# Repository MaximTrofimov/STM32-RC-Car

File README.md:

# STM32-RC-Car
RC car with manual and autonomous modes, dual STM32 wireless communication (remote and car PCBs).

## Demo Videos

**Manual Mode**

**Autonomous Mode**

## Photos

**RC Car and Remote**

**Remote and Car PCBs**

## Overview
- Designed two custom PCBs (remote and car) for a wirelessly-controlled RC car
- Implemented wireless communication between two STM32 microcontrollers using embedded firmware (HAL library)
- Developed manual and autonomous modes

## Hardware
- STM32F446RE (x2 - one in car, one in remote)
- NucleoF446RE (x2 - prototyping)
- NRF24L01+PA+LNA wireless transceiver modules (x2 - one for car, one for remote)
- HC-SR04 ultrasonic sensor (x3 - front, left, right)
- SG90 servo motor (steering)
- TB6612FNG dual H-bridge motor driver (RWD)
- TT dual DC motor 3-6V (x2)
- KY-023 dual-axis analog joystick (remote)
- Custom PCBs (x2 - one for car, one for remote)
- 2S Lipo battery (car)
- 1s Li Ion battery (remote)

## Repo Structure
```
Firmware/
  car_mcu/       - STM32 embedded firmware for the car MCU
  remote_mcu/    - STM32 embedded firmware for the remote MCU
Hardware/
  car_pcb/       - Car PCB, schematic, BOM
  remote_pcb/    - Remote PCB, schematic, BOM
Mechanical/       - Wheels and steering servo enclosure CAD files (STEP)
```

## How It Works

**Manual Mode:**
The X and Y coordinates of the joystick position are read into a two variable array, VR. The array is then transmitted alongside each packet using the remote PCB's NRF24L01 module, and received at the car PCB's NRF24L01 module. The DC Motors are controlled using the TB6612FNG where a maximum joystick value results in fully duty cycle, a neutral results in zero duty cycle, and a minimum results in maximum duty cycle spinning the motors the other way. The SG90 steering is controlled via a timer for PWM. If the joystick is extended to the far right or far left, the NRF24L01 sends a larger joystick value and therefore the pulse is set to high for longer. Both throttle and steering respond to the specific displacement of the joystick from its absolute center, giving it the ability to control speed, and steering degree. The firmware dictates what part of the packet is responsible for motors, what part for the steering angle, and what part for the mode, which is triggered via an interrupt. 

**Autonomous Mode:**
If the joystick button is pressed, the mode is toggled to autonomous. Motors begin by running on half duty cycle and steering is set to a constant of about 20 degrees. The front, left, and right ultrasonic sensors notify the microcontroller when an obstacle is a certain distance away. Once this happens the car stops, checks its sides, goes back, and turns to the side where there is more free space. 

## Firmware Configuration

**Car MCU**

**Remote MCU**

## PCB Design

**Car PCB**

**Remote PCB**

## Breadboard Prototyping

## Power

**Car PCB**
- 2S Lipo -> 3.3V (500 mA rating, STM32, NRF24L01, TB6612FNG logic): TPS62152RGTR, reference schematic on Texas Instruments Power Designer.
- 2S Lipo -> 5V (2A rating, TB6612FNG motor power, SG90, HCSR04): TPS82130SILR, reference schematic on Texas Instruments Power Designer.

**Remote PCB**
- 1S Li-Ion -> 3.3V (600 mA rating, STM32, KY-023, NRF24L01): AP2112K-3.3TRG1, reference schematic on datasheet. Used LDO due to lower voltage difference. 

## Credits
- Shawn Hymel STM32 Tutorial Series [https://www.youtube.com/watch?v=hyZS2p1tW-g&list=PLEBQazB0HUyRYuzfi4clXsKUSgorErmBv]
- Phil's Lab KiCad Tutorial [https://www.youtube.com/watch?v=aVUqaB0IMh4]
- NRF24L01 Tutorial Series [https://www.youtube.com/watch?v=mB7LsiscM78&t=996s]
- HCSR04 Tutorial Article [https://controllerstech.com/hcsr04-ultrasonic-sensor-and-stm32/]
- SG90 Tutorial Article [https://controllerstech.com/servo-motor-with-stm32/]
- TB6612FNG Tutorial Video [https://www.youtube.com/watch?v=zWYYvtU8Wt4]
- Joystick Module Tutorial Article [https://controllerstech.com/joystick-and-stm32/]
- Texas Instruments 2S Lipo -> 3.3V Buck Converter Circuit [https://webench.ti.com/power-designer/switching-regulator/customize/5?noparams=0]
- Texas Instruments 2S Lipo -> 5V Buck Converter Circuit [https://webench.ti.com/power-designer/switching-regulator/customize/6?noparams=0]

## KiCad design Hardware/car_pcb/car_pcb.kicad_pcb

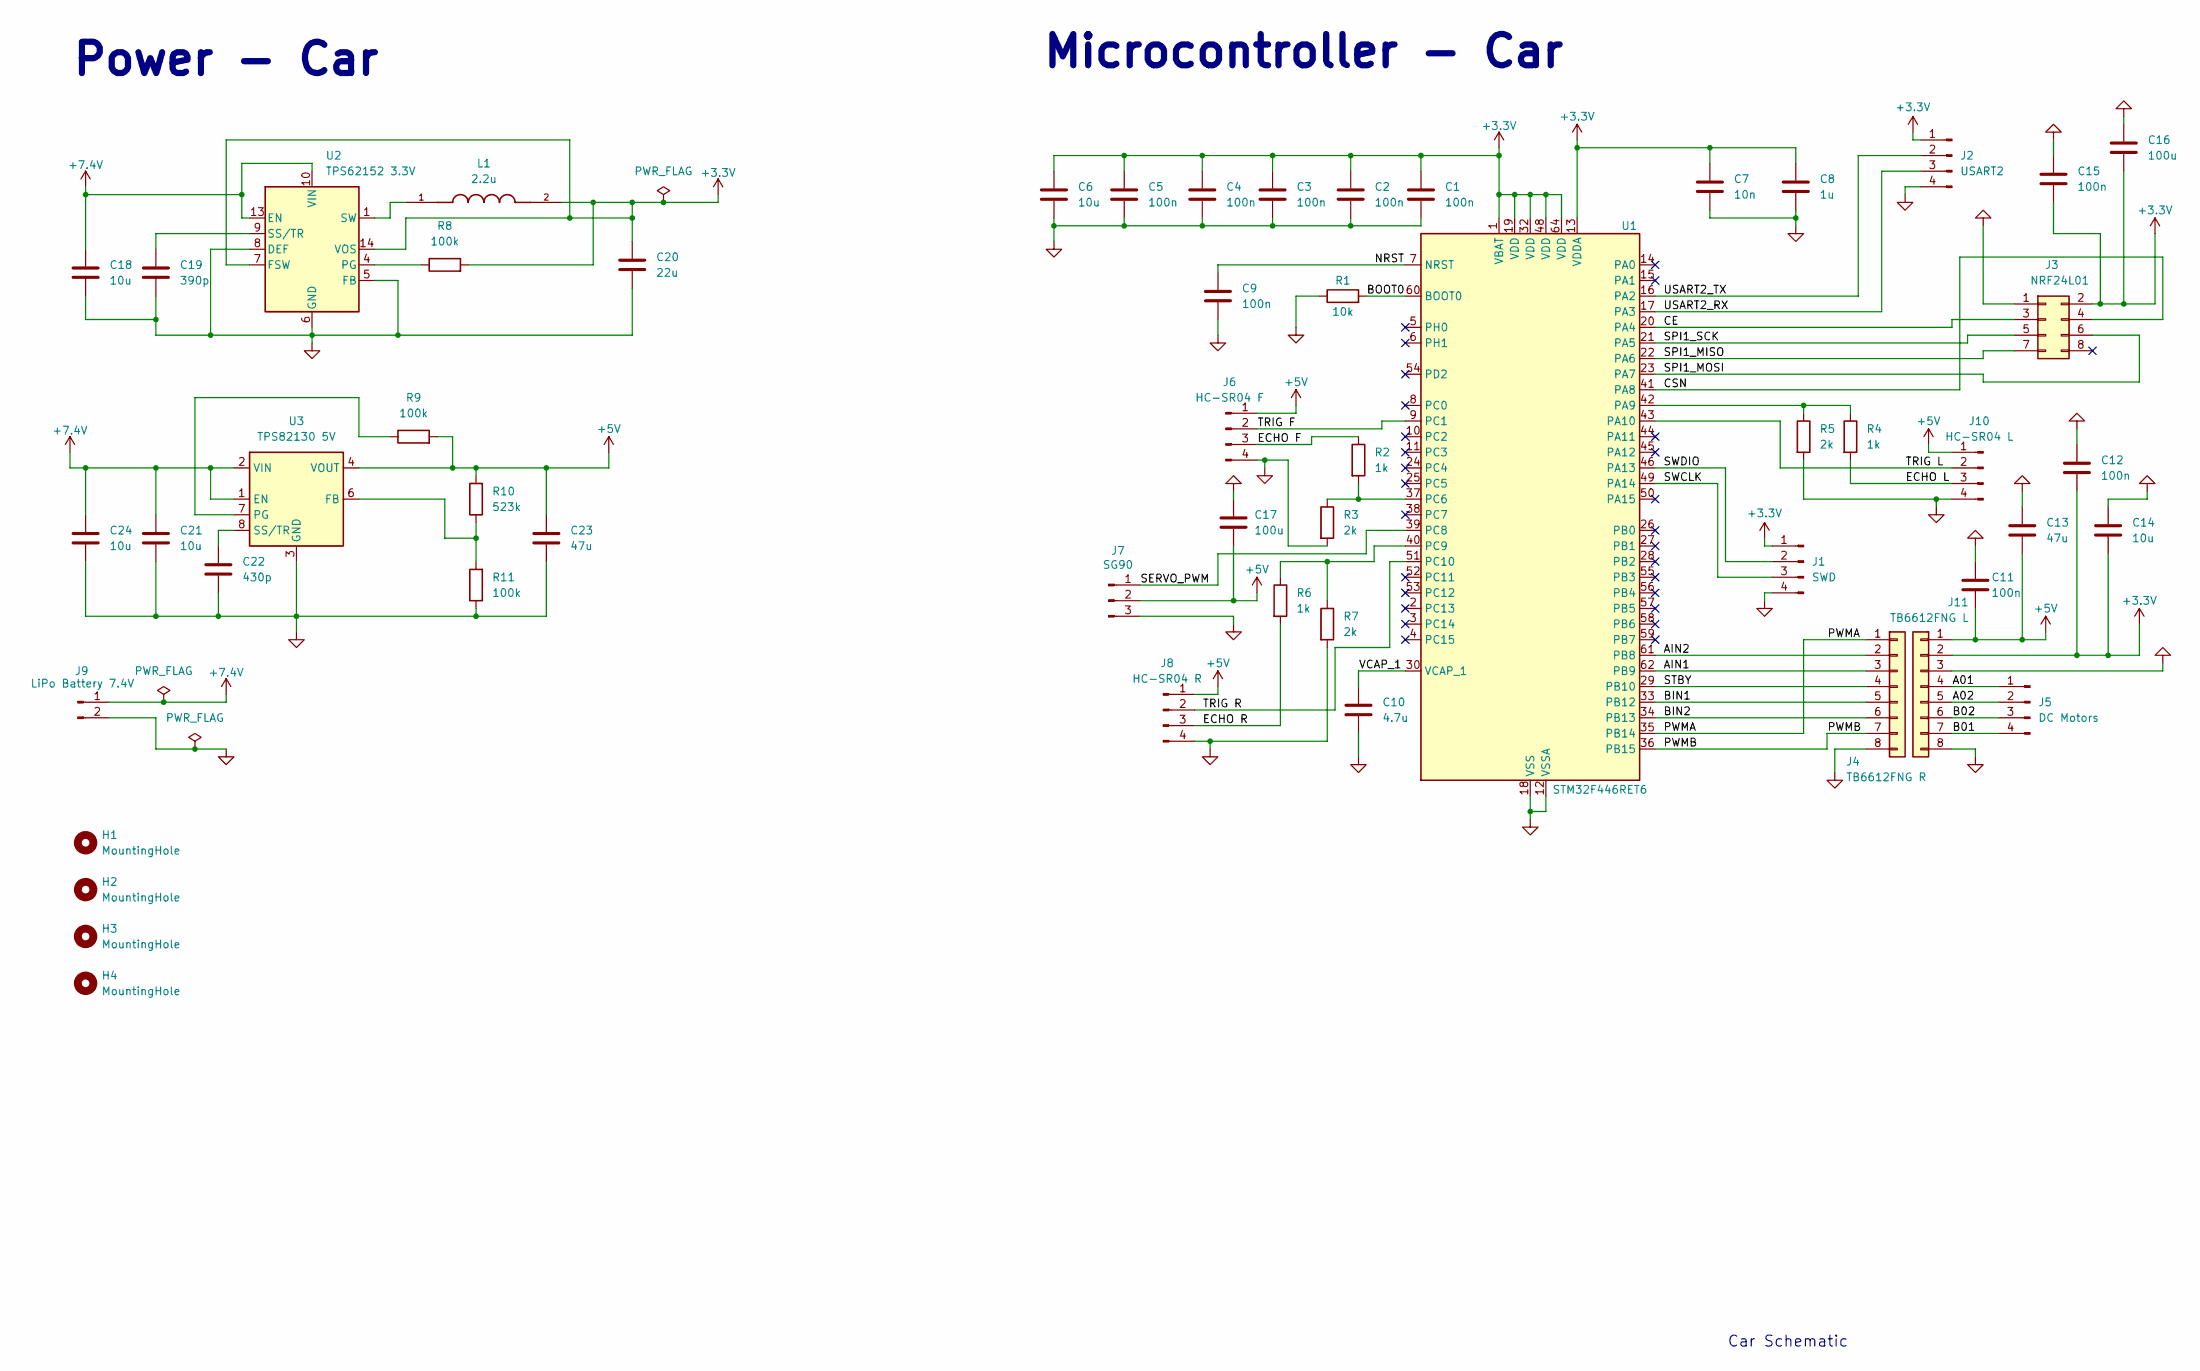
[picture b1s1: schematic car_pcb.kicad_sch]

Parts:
C1, C2, C3, C4, C5, C9, C11, C12, C15: 100n; C_0805_2012Metric; LCSC C49678
C6, C14, C18, C21, C24: 10u; C_0805_2012Metric; LCSC C15850
C7: 10n; C_0805_2012Metric; LCSC C1710
C8: 1u; C_0805_2012Metric; LCSC C28323
C10: 4.7u; C_0805_2012Metric; LCSC C1779
C13, C23: 47u; C_Radial_D5.0mm_H11.0mm_P2.00mm
C16, C17: 100u; C_Radial_D5.0mm_H11.0mm_P2.00mm
C19: 390p; C_0805_2012Metric; LCSC C1741
C20: 22u; C_0805_2012Metric; LCSC C45783
C22: 430p; C_0805_2012Metric; LCSC C67898
H1, H2, H3, H4: MountingHole; MountingHole_2.2mm_M2
J1: SWD; PinHeader_1x04_P2.54mm_Vertical
J2: USART2; PinHeader_1x04_P2.54mm_Vertical
J3: NRF24L01; PinHeader_2x04_P2.54mm_Vertical
J4: TB6612FNG R; PinHeader_1x08_P2.54mm_Vertical
J5: DC Motors; PinHeader_1x04_P2.54mm_Vertical
J6: HC-SR04 F; PinHeader_1x04_P2.54mm_Vertical
J7: SG90; PinHeader_1x03_P2.54mm_Vertical
J8: HC-SR04 R; PinHeader_1x04_P2.54mm_Vertical
J9: LiPo Battery 7.4V; PinHeader_1x02_P2.54mm_Vertical
J10: HC-SR04 L; PinHeader_1x04_P2.54mm_Vertical
J11: TB6612FNG L; PinHeader_1x08_P2.54mm_Vertical
L1: 2.2u; IND_VLS3012CX-2R2M-1; PARTREV N/A; DigiKey_Part_Number 445-180922-1-ND
R1: 10k; R_0805_2012Metric; LCSC C176201
R2, R4, R6: 1k; R_0805_2012Metric; LCSC C17513
R3, R5, R7: 2k; R_0805_2012Metric; LCSC C17604
R8, R9, R11: 100k; R_0805_2012Metric; LCSC C25611
R10: 523k; R_0805_2012Metric; LCSC C17742
U1: STM32F446RET6; LQFP-64_10x10mm_P0.5mm; LCSC C69336
U2: TPS62152 3.3V; VQFN-16-1EP_3x3mm_P0.5mm_EP1.68x1.68mm_ThermalVias; LCSC C2070611
U3: TPS82130 5V; Texas_SIL0008D_MicroSiP-8-1EP_2.8x3mm_P0.65mm_EP1.1x1.9mm_T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; LCSC C473914

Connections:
+3.3V: C1.1, C2.1, C3.1, C4.1, C5.1, C6.1, C7.1, C8.1, C12.2, C14.2, C15.2, C16.2, C20.1, J1.1, J2.1, J3.2, J11.2, L1.2, R8.2, U1.1 (VBAT), U1.13 (VDDA), U1.19 (VDD), U1.32 (VDD), U1.48 (VDD), U1.64 (VDD), U2.7 (FSW), U2.14 (VOS); also elsewhere on the board
+5V: C11.2, C13.2, C17.2, C23.1, J6.1, J7.2, J8.1, J10.1, J11.1, R9.2, R10.2, U3.4 (VOUT), U3.5 (VOUT); also elsewhere on the board
+7.4V: C18.1, C21.1, C24.1, J9.1, U2.10 (VIN), U2.11 (VIN), U2.12 (VIN), U2.13 (EN), U3.1 (EN), U3.2 (VIN)
/A01: J5.1, J11.4; also elsewhere on the board
/A02: J5.2, J11.5; also elsewhere on the board
/AIN1: J4.3, U1.62 (PB9)
/AIN2: J4.2, U1.61 (PB8)
/B01: J5.4, J11.7; also elsewhere on the board
/B02: J5.3, J11.6; also elsewhere on the board
/BIN1: J4.5, U1.33 (PB12)
/BIN2: J4.6, U1.34 (PB13)
/BOOT0: R1.2, U1.60 (BOOT0)
/CE: J3.3, U1.20 (PA4)
/CSN: J3.4, U1.41 (PA8)
/ECHO F: J6.3, R2.1
/ECHO L: J10.3, R4.2; also elsewhere on the board
/ECHO R: J8.3, R6.2; also elsewhere on the board
/NRST: C9.1, U1.7 (NRST)
/PWMA: J4.1, U1.35 (PB14)
/PWMB: J4.7, U1.36 (PB15)
/SERVO_PWM: J7.1, U1.39 (PC8)
/SPI1_MISO: J3.7, U1.22 (PA6)
/SPI1_MOSI: J3.6, U1.23 (PA7)
/SPI1_SCK: J3.5, U1.21 (PA5)
/STBY: J4.4, U1.29 (PB10)
/SWCLK: J1.3, U1.49 (PA14)
/SWDIO: J1.2, U1.46 (PA13)
/TRIG F: J6.2, U1.9 (PC1)
/TRIG L: J10.2, U1.43 (PA10); also elsewhere on the board
/TRIG R: J8.2, U1.51 (PC10); also elsewhere on the board
/USART2_RX: J2.3, U1.17 (PA3)
/USART2_TX: J2.2, U1.16 (PA2)
/VCAP_1: C10.1, U1.30 (VCAP_1)
GND: C1.2, C2.2, C3.2, C4.2, C5.2, C6.2, C7.2, C8.2, C9.2, C10.2, C11.1, C12.1, C13.1, C14.1, C15.1, C16.1, C17.1, C18.2, C19.2, C20.2, C21.2, C22.2, C23.2, C24.2, J1.4, J2.4, J3.1, J4.8, J6.4, J7.3, J8.4, J9.2, J10.4, J11.3, J11.8, R1.1, R3.2, R5.2, R7.2, R11.1, U1.12 (VSSA), U1.18 (VSS), U1.31 (VSS), U1.47 (VSS), U1.63 (VSS), U2.5 (FB), U2.6 (GND), U2.8 (DEF), U2.15 (GND), U2.16 (GND), U2.17 (GND), U3.3 (GND), U3.9 (GND); also elsewhere on the board
unnamed: L1.1, U2.1 (SW), U2.2 (SW), U2.3 (SW)
unnamed: R4.1, R5.1, U1.42 (PA9)
unnamed: R2.2, R3.1, U1.37 (PC6)
unnamed: R6.1, R7.1, U1.40 (PC9)
unnamed: R8.1, U2.4 (PG)
unnamed: C19.1, U2.9 (SS/TR)
unnamed: R10.1, R11.2, U3.6 (FB)
unnamed: R9.1, U3.7 (PG)
unnamed: C22.1, U3.8 (SS/TR)

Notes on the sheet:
Microcontroller - Car
Car Schematic
Power - Car

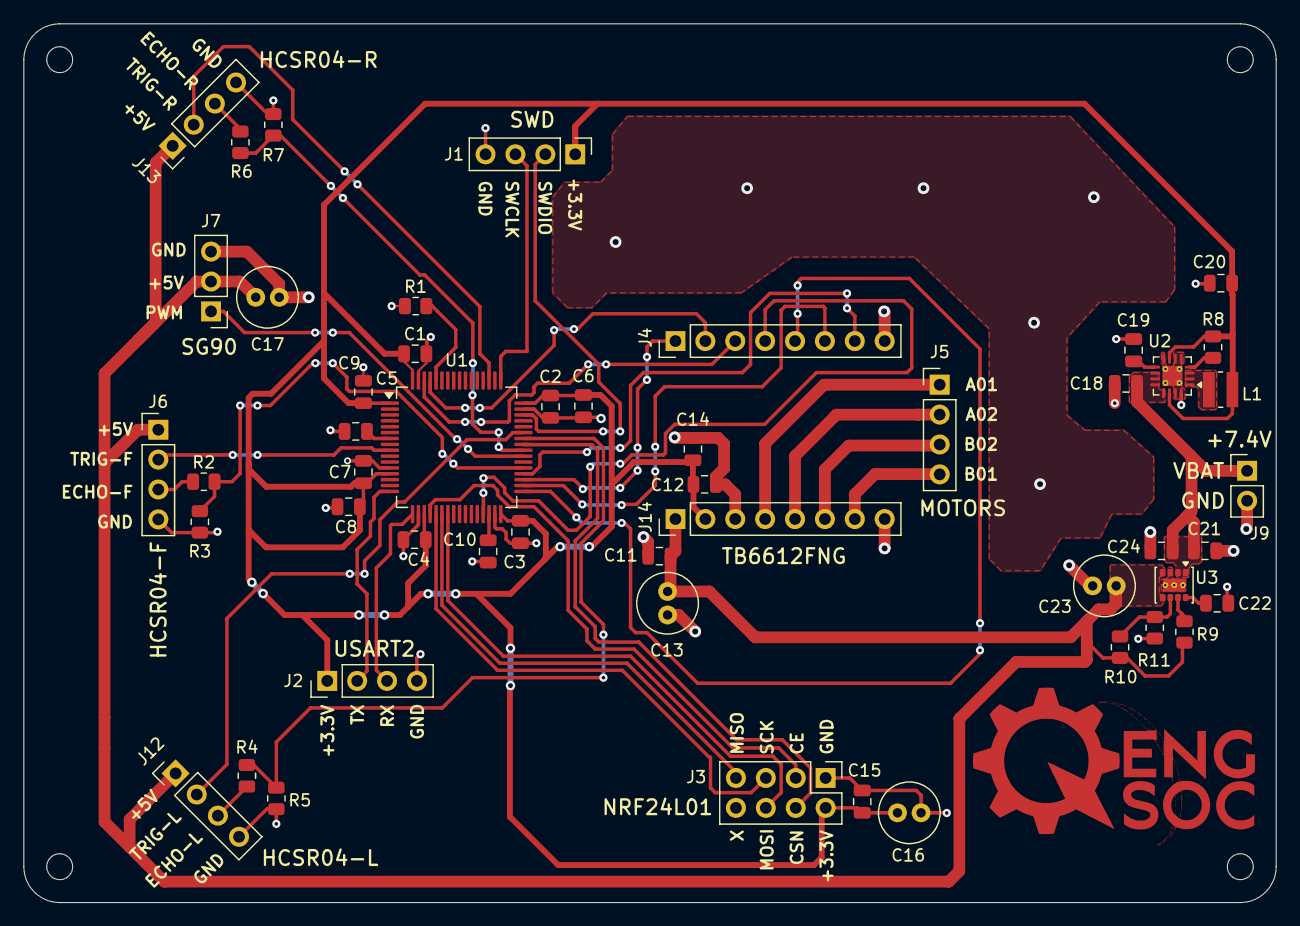
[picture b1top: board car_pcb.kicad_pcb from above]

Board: 2 copper layers, 106.4 x 74.7 mm, 54 parts (0 on the bottom side), 43 nets.

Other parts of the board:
J12: HC-SR04 L; PinHeader_1x04_P2.54mm_Vertical
J13: HC-SR04 R; PinHeader_1x04_P2.54mm_Vertical
J14: TB6612FNG L; PinHeader_1x08_P2.54mm_Vertical

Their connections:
+3.3V: J14.2; also elsewhere on the board
+5V: J12.1, J13.1, J14.1; also elsewhere on the board
/A01: J14.4; also elsewhere on the board
/A02: J14.5; also elsewhere on the board
/B01: J14.7; also elsewhere on the board
/B02: J14.6; also elsewhere on the board
/ECHO L: J12.3; also elsewhere on the board
/ECHO R: J13.3; also elsewhere on the board
/TRIG L: J12.2; also elsewhere on the board
/TRIG R: J13.2; also elsewhere on the board
GND: J12.4, J13.4, J14.3, J14.8; also elsewhere on the board

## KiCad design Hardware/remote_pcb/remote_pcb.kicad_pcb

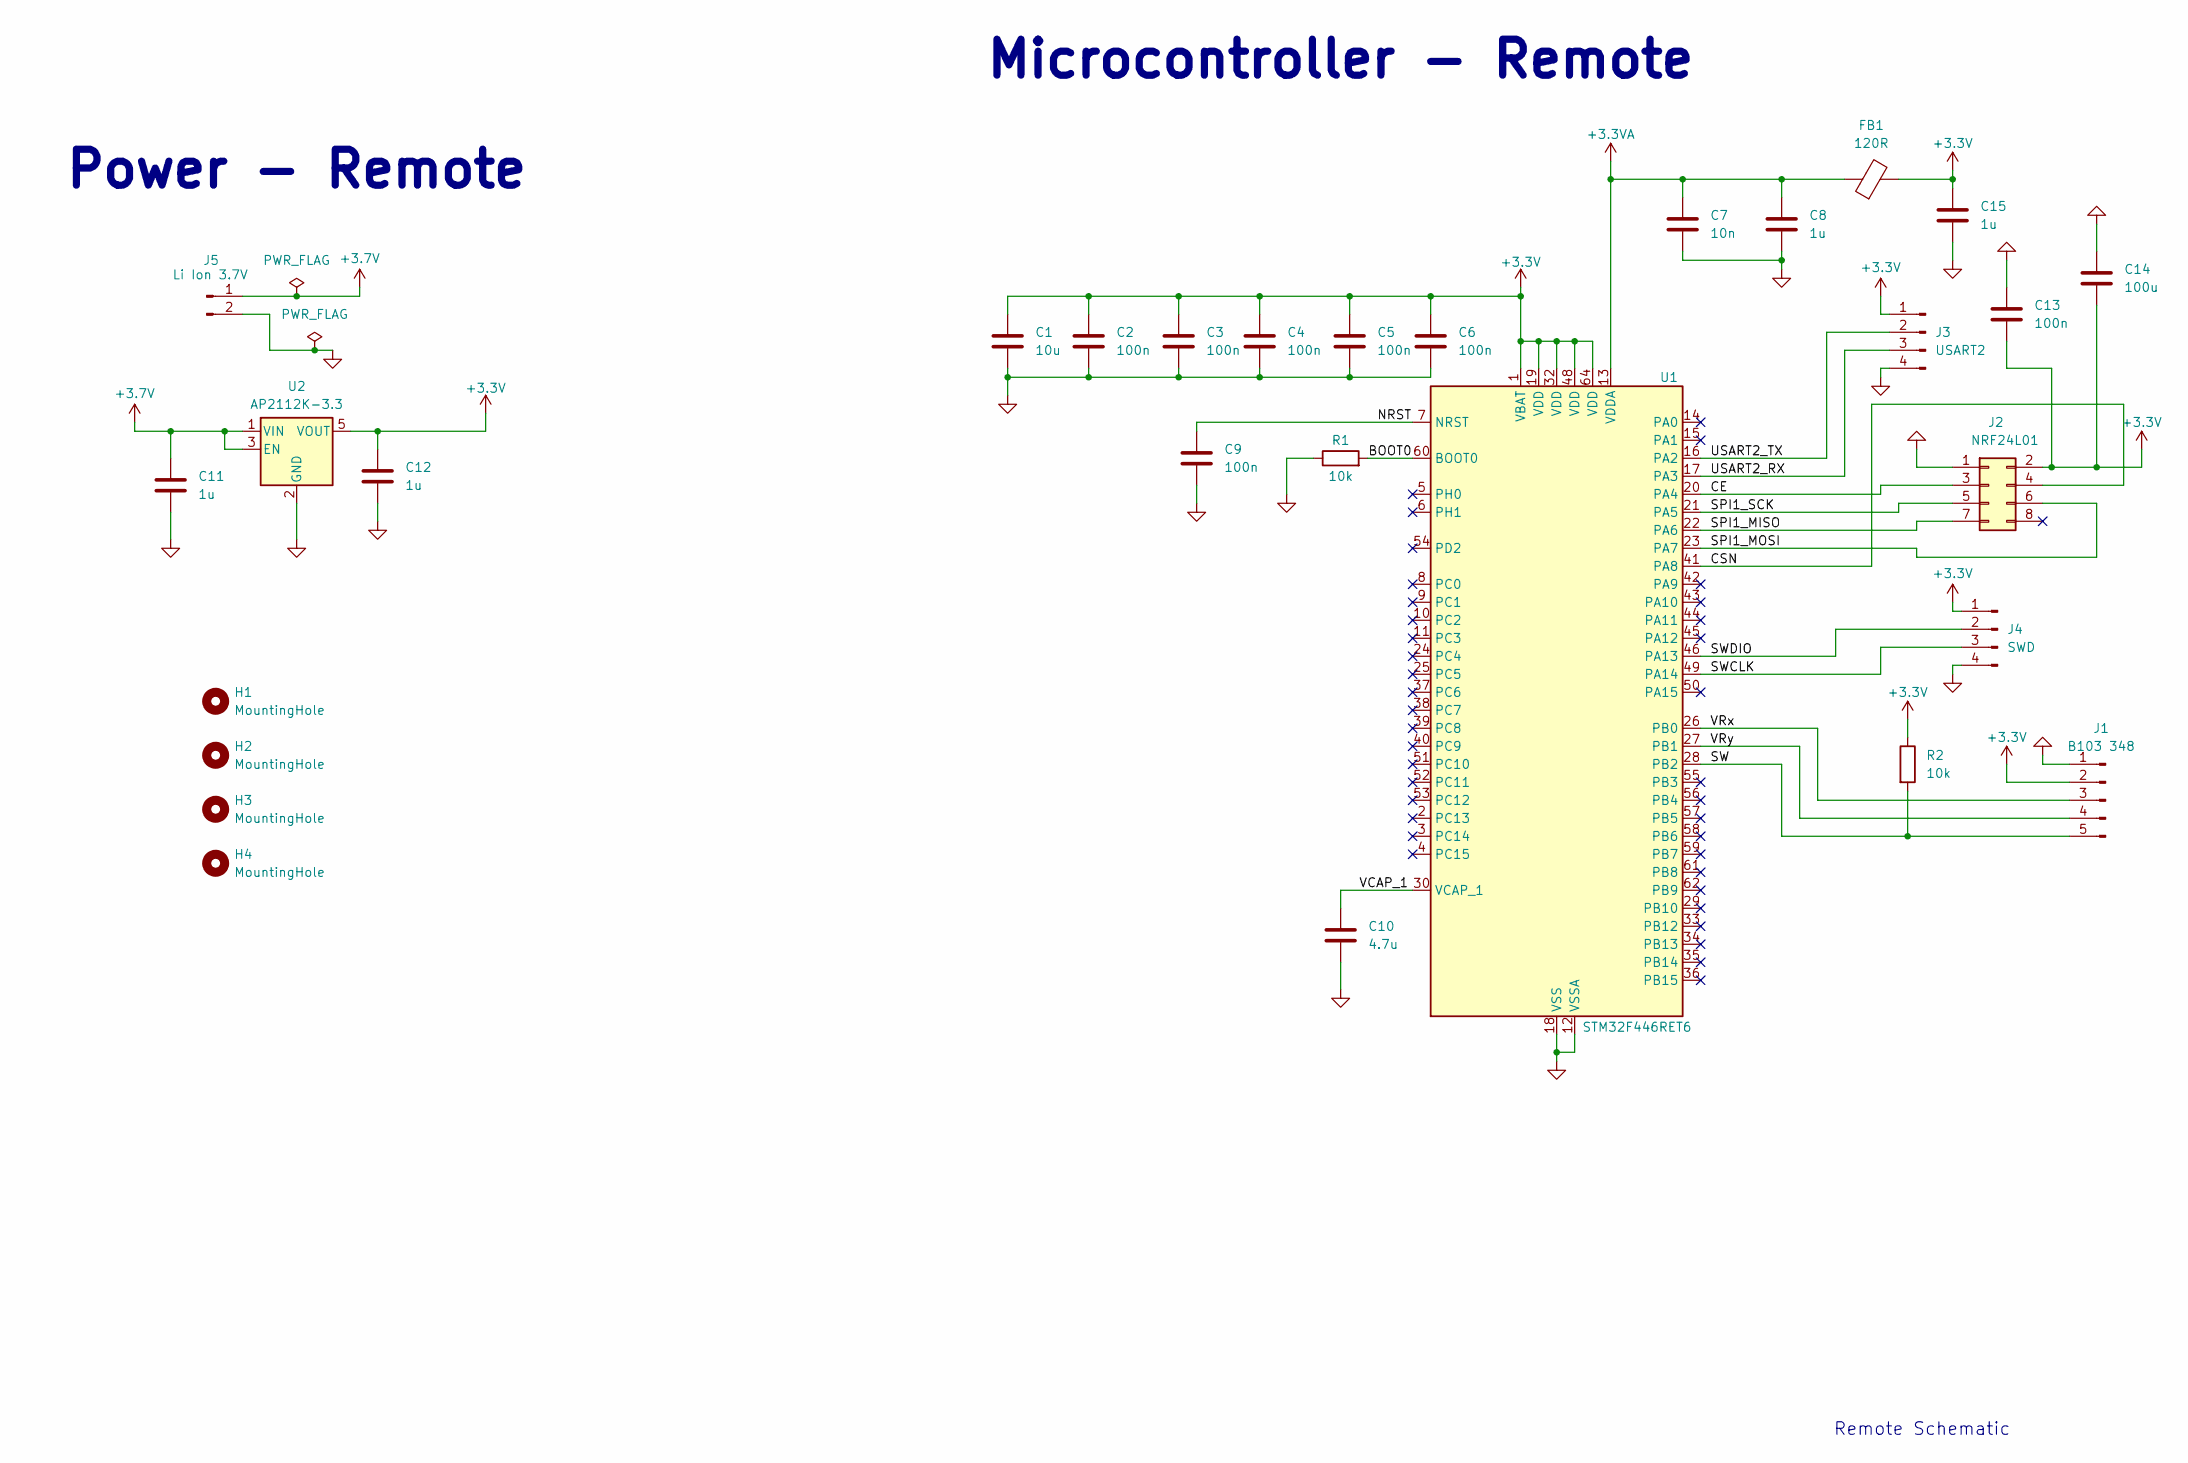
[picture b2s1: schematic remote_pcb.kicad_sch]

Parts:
C1: 10u; C_0805_2012Metric; LCSC C15850
C2, C3, C4, C5, C6, C9, C13: 100n; C_0805_2012Metric; LCSC C49678
C7: 10n; C_0805_2012Metric; LCSC C1710
C8, C11, C12, C15: 1u; C_0805_2012Metric; LCSC C28323
C10: 4.7u; C_0805_2012Metric; LCSC C1779
C14: 100u; C_Radial_D5.0mm_H11.0mm_P2.00mm
FB1: 120R; L_0805_2012Metric; LCSC C79382
H1, H2, H3, H4: MountingHole; MountingHole_2.2mm_M2
J1: B103 348; PinHeader_1x05_P2.54mm_Vertical
J2: NRF24L01; PinHeader_2x04_P2.54mm_Vertical
J3: USART2; PinHeader_1x04_P2.54mm_Vertical
J4: SWD; PinHeader_1x04_P2.54mm_Vertical
J5: Li Ion 3.7V; JST_XH_B2B-XH-A_1x02_P2.50mm_Vertical
R1, R2: 10k; R_0805_2012Metric; LCSC C176201
U1: STM32F446RET6; LQFP-64_10x10mm_P0.5mm; LCSC C69336
U2: AP2112K-3.3; SOT-23-5; LCSC C51118

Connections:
+3.3V: C1.1, C2.1, C3.1, C4.1, C5.1, C6.1, C12.1, C13.2, C14.2, C15.1, FB1.2, J1.2, J2.2, J3.1, J4.1, R2.1, U1.1 (VBAT), U1.19 (VDD), U1.32 (VDD), U1.48 (VDD), U1.64 (VDD), U2.5 (VOUT)
+3.3VA: C7.1, C8.1, FB1.1, U1.13 (VDDA)
+3.7V: C11.1, J5.1, U2.1 (VIN), U2.3 (EN)
/BOOT0: R1.2, U1.60 (BOOT0)
/CE: J2.3, U1.20 (PA4)
/CSN: J2.4, U1.41 (PA8)
/NRST: C9.1, U1.7 (NRST)
/SPI1_MISO: J2.7, U1.22 (PA6)
/SPI1_MOSI: J2.6, U1.23 (PA7)
/SPI1_SCK: J2.5, U1.21 (PA5)
/SW: J1.5, R2.2, U1.28 (PB2)
/SWCLK: J4.3, U1.49 (PA14)
/SWDIO: J4.2, U1.46 (PA13)
/USART2_RX: J3.3, U1.17 (PA3)
/USART2_TX: J3.2, U1.16 (PA2)
/VCAP_1: C10.1, U1.30 (VCAP_1)
/VRx: J1.3, U1.26 (PB0)
/VRy: J1.4, U1.27 (PB1)
GND: C1.2, C2.2, C3.2, C4.2, C5.2, C6.2, C7.2, C8.2, C9.2, C10.2, C11.2, C12.2, C13.1, C14.1, C15.2, J1.1, J2.1, J3.4, J4.4, J5.2, R1.1, U1.12 (VSSA), U1.18 (VSS), U1.31 (VSS), U1.47 (VSS), U1.63 (VSS), U2.2 (GND)

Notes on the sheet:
Power - Remote
Microcontroller - Remote
Remote Schematic

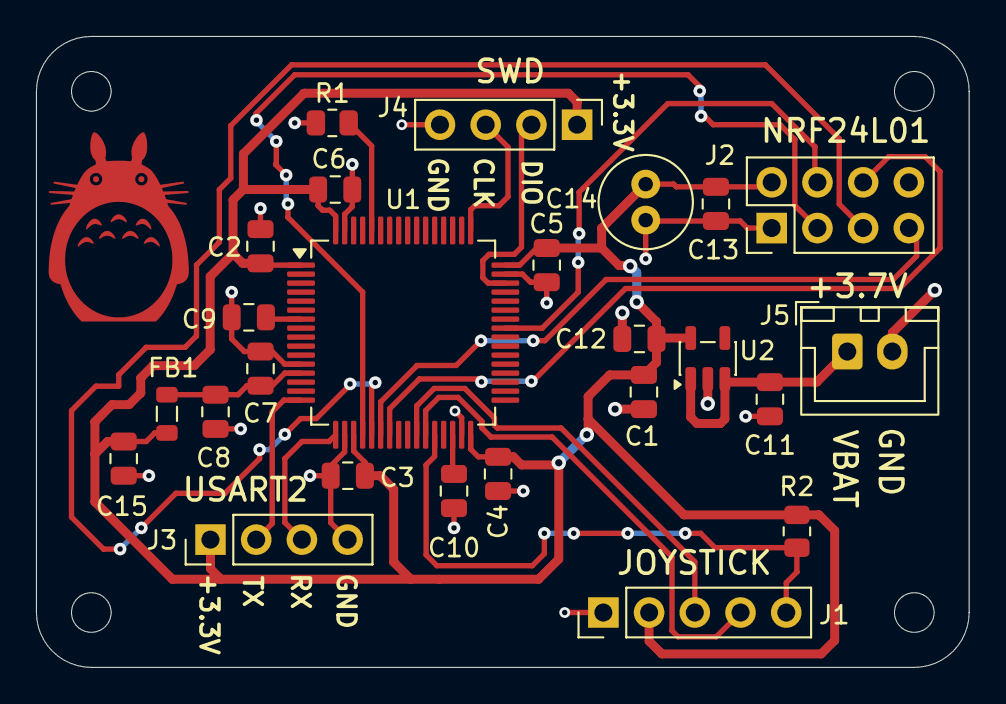
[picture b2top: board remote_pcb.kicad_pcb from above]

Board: 2 copper layers, 51.8 x 35.1 mm, 29 parts (0 on the bottom side), 19 nets.

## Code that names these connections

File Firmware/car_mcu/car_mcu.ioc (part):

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Mcu.Name=STM32F446R(C-E)Tx
Mcu.Package=LQFP64
Mcu.UserName=STM32F446RETx
PA10.Signal=GPIO_Output
PA13.Mode=Serial_Wire
PA13.Signal=SYS_JTMS-SWDIO
PA14.Mode=Serial_Wire
PA14.Signal=SYS_JTCK-SWCLK
PA2.Mode=Asynchronous
PA2.Signal=USART2_TX
PA3.Mode=Asynchronous
PA3.Signal=USART2_RX
PA4.GPIOParameters=GPIO_Speed,GPIO_Label
PA4.GPIO_Label=CE
PA4.GPIO_Speed=GPIO_SPEED_FREQ_HIGH
PA4.Signal=GPIO_Output
PA5.Mode=Full_Duplex_Master
PA5.Signal=SPI1_SCK
PA6.Mode=Full_Duplex_Master
PA6.Signal=SPI1_MISO
PA7.Mode=Full_Duplex_Master
PA7.Signal=SPI1_MOSI
PA8.GPIOParameters=GPIO_Speed,GPIO_Label
PA8.GPIO_Label=CSN
PA8.GPIO_Speed=GPIO_SPEED_FREQ_HIGH
PA8.Signal=GPIO_Output
PA9.Signal=S_TIM1_CH2
PB10.Signal=GPIO_Output
PB12.Signal=GPIO_Output
PB13.Signal=GPIO_Output
PB14.Signal=S_TIM12_CH1
PB15.Signal=S_TIM12_CH2
PB8.Signal=GPIO_Output
PB9.Signal=GPIO_Output
PC1.Signal=GPIO_Output
PC10.Signal=GPIO_Output
PC6.Signal=S_TIM8_CH1
PC8.Signal=S_TIM3_CH3
PC9.Signal=S_TIM8_CH4
RCC.SYSCLKFreq_VALUE=180000000
RCC.SYSCLKSource=RCC_SYSCLKSOURCE_PLLCLK
board=custom

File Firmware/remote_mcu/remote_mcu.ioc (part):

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Mcu.Name=STM32F446R(C-E)Tx
Mcu.Package=LQFP64
Mcu.UserName=STM32F446RETx
PA13.Mode=Serial_Wire
PA13.Signal=SYS_JTMS-SWDIO
PA14.Mode=Serial_Wire
PA14.Signal=SYS_JTCK-SWCLK
PA2.Mode=Asynchronous
PA2.Signal=USART2_TX
PA3.Mode=Asynchronous
PA3.Signal=USART2_RX
PA4.GPIOParameters=GPIO_Speed,GPIO_Label
PA4.GPIO_Label=CE
PA4.GPIO_Speed=GPIO_SPEED_FREQ_HIGH
PA4.Signal=GPIO_Output
PA5.Mode=Full_Duplex_Master
PA5.Signal=SPI1_SCK
PA6.Mode=Full_Duplex_Master
PA6.Signal=SPI1_MISO
PA7.Mode=Full_Duplex_Master
PA7.Signal=SPI1_MOSI
PA8.GPIOParameters=GPIO_Speed,GPIO_Label
PA8.GPIO_Label=CSN
PA8.GPIO_Speed=GPIO_SPEED_FREQ_HIGH
PA8.Signal=GPIO_Output
PB0.Signal=ADCx_IN8
PB1.Signal=ADCx_IN9
PB2.GPIOParameters=GPIO_ModeDefaultEXTI
PB2.GPIO_ModeDefaultEXTI=GPIO_MODE_IT_FALLING
PB2.Signal=GPXTI2
RCC.SYSCLKFreq_VALUE=180000000
RCC.SYSCLKSource=RCC_SYSCLKSOURCE_PLLCLK
board=custom

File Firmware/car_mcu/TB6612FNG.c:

/*
 * TB6612FNG.c
 *
 *  Created on: Jun 15, 2026
 */


// the TB6612FNG code was taken from [https://www.youtube.com/watch?v=zWYYvtU8Wt4] and modified to fit the joystick module.


#include "stm32f4xx_hal.h"
#include "TB6612FNG.h"
#include "main.h"

extern TIM_HandleTypeDef htim12;

void Motors(uint32_t Joystick_val) {

	uint16_t duty_cycle = 0;

	HAL_GPIO_WritePin(GPIOB, GPIO_PIN_10, 1); // STBY off, working

	if (Joystick_val < 2000) {
		//backwards

		duty_cycle = ((2000 - Joystick_val) * 1000) / 2000;

		__HAL_TIM_SET_COMPARE(&htim12, TIM_CHANNEL_1, duty_cycle);
		__HAL_TIM_SET_COMPARE(&htim12, TIM_CHANNEL_2, duty_cycle);

		HAL_GPIO_WritePin(GPIOB, GPIO_PIN_9, 1); // AIN1 low
		HAL_GPIO_WritePin(GPIOB, GPIO_PIN_8, 0); // AIN2 high (bwd)

		HAL_GPIO_WritePin(GPIOB, GPIO_PIN_12, 0); // BIN1 low
		HAL_GPIO_WritePin(GPIOB, GPIO_PIN_13, 1); // BIN2 high (bwd)
	}

	if ((Joystick_val >= 2000) && (Joystick_val <= 2200)) {
		//motors off

		__HAL_TIM_SET_COMPARE(&htim12, TIM_CHANNEL_1, 0); // stops timer
		__HAL_TIM_SET_COMPARE(&htim12, TIM_CHANNEL_2, 0);

		HAL_GPIO_WritePin(GPIOB, GPIO_PIN_9, 0); // stop
		HAL_GPIO_WritePin(GPIOB, GPIO_PIN_8, 0);

		HAL_GPIO_WritePin(GPIOB, GPIO_PIN_12, 0); // stop
		HAL_GPIO_WritePin(GPIOB, GPIO_PIN_13, 0);

	}

	if (Joystick_val > 2200) {
		//forwards

		duty_cycle = ((Joystick_val - 2200) * 1000) / (4095 - 2200);

		__HAL_TIM_SET_COMPARE(&htim12, TIM_CHANNEL_1, duty_cycle);
		__HAL_TIM_SET_COMPARE(&htim12, TIM_CHANNEL_2, duty_cycle);

		HAL_GPIO_WritePin(GPIOB, GPIO_PIN_9, 0); // AIN1 low
		HAL_GPIO_WritePin(GPIOB, GPIO_PIN_8, 1); // AIN2 high (fwd)

		HAL_GPIO_WritePin(GPIOB, GPIO_PIN_12, 1); // BIN1 low
		HAL_GPIO_WritePin(GPIOB, GPIO_PIN_13, 0); // BIN2 high (fwd)
	}
}
